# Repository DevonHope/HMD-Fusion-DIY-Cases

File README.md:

# HMD-Fusion-DIY-Cases
A repo for storing my progress into developing a case/outift for the HMD Fusion phone. This repo includes schematic drawings, PCB drawings, and 3D models for the breakout board and testbench case. This repo will also include future dev kits for cases/outfits that make use of the exposed pins on the back of the HMD Fusion.

## TO DO
- Test pins for continuity and stability
- Develop a USB 2.0 circuit for expanding the I/O into a modular phone case

## I/O breakout board

KiCAD V8 PCB drawing

The breakout board is used to breakout the 6 pin header on the back of the phone and expand it into the ISO standard 2.54mm/0.1" 6 pin header for breadboard testing and development of external circuits. This board should be manufactured using a flexible PCB material, the case and basic funcationality of the spring pins were designed with this in mind. 

KiCAD V8 3D Model Drawing

## Testbench Case

There is a testbench case to go with this, it is best printed in TPU or other flexible materials to ensure the spring loaded pins on the breakout board do not get bent or damaged when removing the phone from the case. To insert the PCB into the case there are three edges that overlap the cutout of the PCB slot, this is a simple method used for the time being to get simple testing done but will be modified for an actual test run of a case/outfit. 

Testbench Case Bottom Half V1R1

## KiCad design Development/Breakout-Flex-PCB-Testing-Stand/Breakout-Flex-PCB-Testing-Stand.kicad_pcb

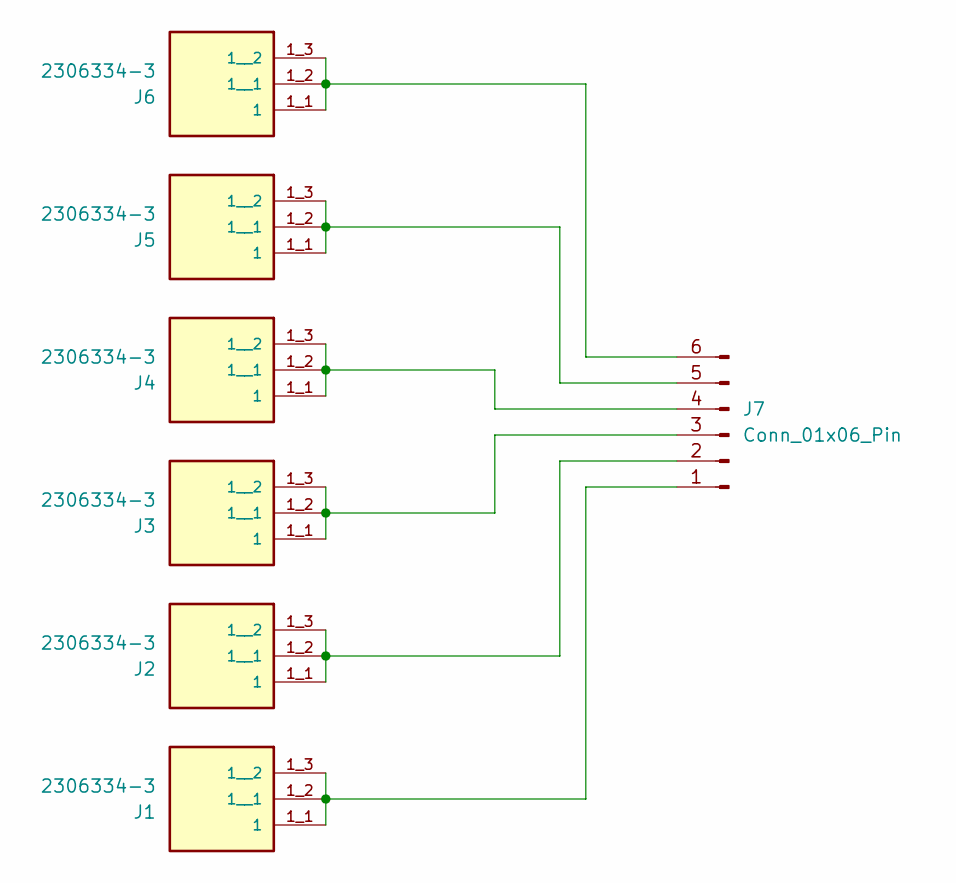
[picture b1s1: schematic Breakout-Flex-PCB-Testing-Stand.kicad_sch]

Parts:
J1, J2, J3, J4, J5, J6: 2306334-3; TE_2306334-3; PARTREV A; LCSC C3308705
J7: Conn_01x06_Pin; PinSocket_1x06_P2.54mm_Vertical; LCSC C492405

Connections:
unnamed: J1.1_1 (1), J1.1_2 (1__1), J1.1_3 (1__2), J7.1
unnamed: J2.1_1 (1), J2.1_2 (1__1), J2.1_3 (1__2), J7.2
unnamed: J3.1_1 (1), J3.1_2 (1__1), J3.1_3 (1__2), J7.3
unnamed: J4.1_1 (1), J4.1_2 (1__1), J4.1_3 (1__2), J7.4
unnamed: J5.1_1 (1), J5.1_2 (1__1), J5.1_3 (1__2), J7.5
unnamed: J6.1_1 (1), J6.1_2 (1__1), J6.1_3 (1__2), J7.6

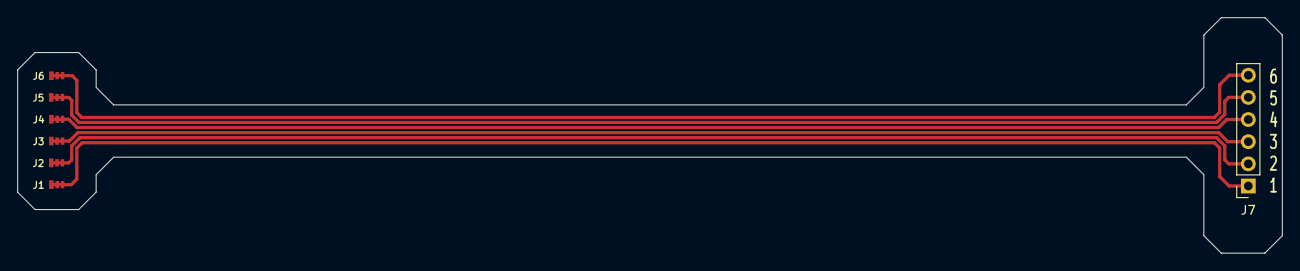
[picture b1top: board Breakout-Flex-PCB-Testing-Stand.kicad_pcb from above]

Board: 2 copper layers, 145.0 x 27.0 mm, 7 parts (0 on the bottom side), 6 nets.

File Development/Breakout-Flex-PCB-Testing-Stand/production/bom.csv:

Designator,Footprint,Quantity,Value,LCSC Part #
"J1, J2, J3, J4, J5, J6",TE_2306334-3,6,2306334-3,C3308705
J7,PinSocket_1x06_P2.54mm_Vertical,1,Conn_01x06_Pin,C492405

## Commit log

2025-06-10 First Push
2025-06-10 added photos of test bench case
2025-06-10 added images of breakout board
2025-06-10 added images to readme
2025-06-10 added titles to images in readme
2025-06-10 change heirarchy of folder
